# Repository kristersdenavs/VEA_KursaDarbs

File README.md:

# VEA_KursaDarbs
Gits kurā atradīsies kursa darbs.

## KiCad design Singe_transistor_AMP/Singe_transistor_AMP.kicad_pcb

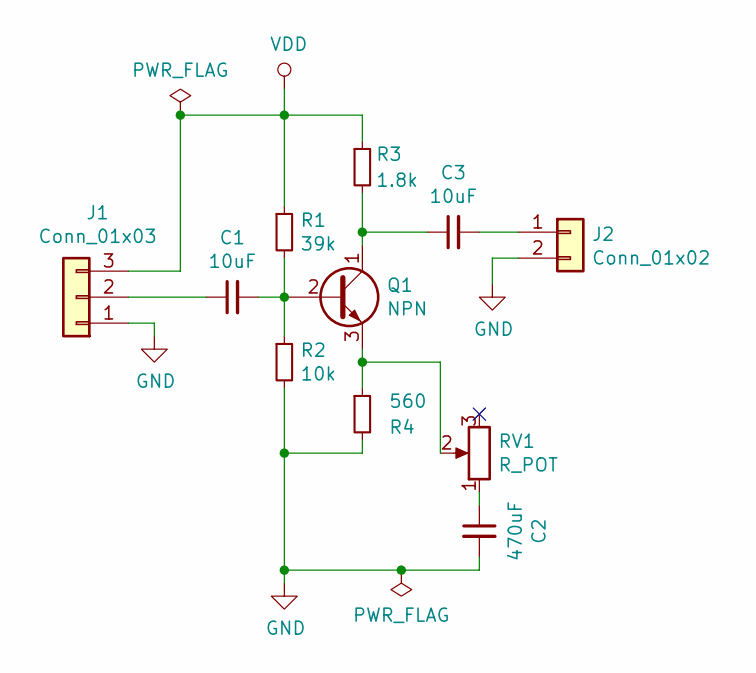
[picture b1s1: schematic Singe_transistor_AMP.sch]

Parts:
C1, C3: 10uF; C_0603_1608Metric
C2: 470uF; CP_Radial_D6.3mm_P2.50mm
J1: Conn_01x03; PinSocket_1x03_P2.54mm_Vertical
J2: Conn_01x02; PinHeader_1x02_P2.54mm_Vertical
Q1: NPN; TO-92
R1: 39k; R_0603_1608Metric
R2: 10k; R_0603_1608Metric
R3: 1.8k; R_0603_1608Metric
R4: 560; R_0603_1608Metric
RV1: R_POT; Potentiometer_ACP_CA6-VSMD_Vertical

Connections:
GND: C2.2, J1.1, J2.2, R2.2, R4.2
unnamed: C1.1, J1.2
unnamed: C1.2, Q1.2 (B), R1.2, R2.1
unnamed: C2.1, RV1.1
unnamed: C3.1, Q1.1 (C), R3.2
unnamed: C3.2, J2.1
unnamed: Q1.3 (E), R4.1, RV1.2
VDD: J1.3, R1.1, R3.1

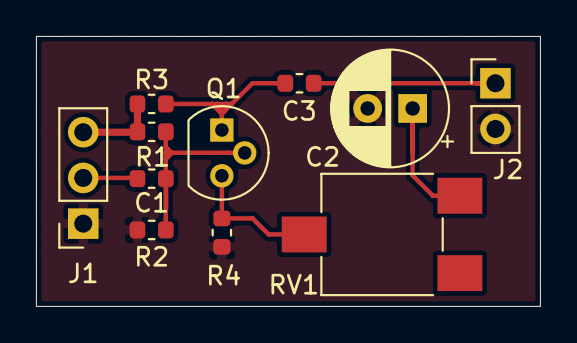
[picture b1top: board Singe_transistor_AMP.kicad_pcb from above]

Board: 2 copper layers, 28.0 x 15.0 mm, 11 parts (0 on the bottom side), 8 nets.

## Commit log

2020-03-03 Pievienots Multivibrators
2020-03-04 Pievienots custom Dual NPN IC
2020-03-16 Pievienots PWR_Supply
2020-03-18 Pievienots Single_transistor_AMP
2020-03-18 Pie Single_transistor_AMP pievienotas komponensu datulapas un NET fails
2020-03-31 Added battery project
2020-04-07 Šet PCB settings
2020-04-21 Made PCB for Single_Transistor_AMP
2020-04-28 updated Single_transistor_AMP
2020-05-05 Single_transistor_amp generated gerber files
2020-05-12 Added BOM for SingleTransAmp
